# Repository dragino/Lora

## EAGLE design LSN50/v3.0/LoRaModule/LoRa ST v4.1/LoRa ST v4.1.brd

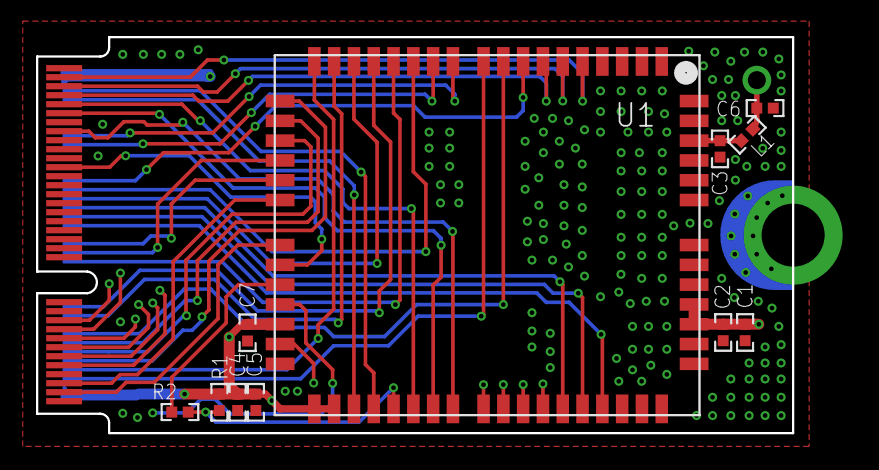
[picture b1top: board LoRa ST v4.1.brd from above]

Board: 4 copper layers, 42.0 x 22.0 mm, 13 parts (1 on the bottom side), 42 nets.

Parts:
C1, C4: 2.2uF; C0402
C2, C5, C7: 0.1uF; C0402
C3, C6: NC; C0402
L1: 9.1nH; L-0402
R1: 10K; R0402
R2: 2K; R0402
U1: LA66_APPLICATION_FRAME
U3: NGFF_M2_KEY_E_CORE; LORA_ST_PCB
U$2: LOGO-SILK-NEW

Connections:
GND: C1.1, C2.2, C3.1, C4.2, C5.1, C6.1, C7.1, U1.3, U1.31, U1.47, U1.48, U1.50, U1.54, U1.55, U1.58, U1.59, U1.61, U1.62, U3.1, U3.18, U3.57, U3.63, U3.75, U3.76
unnamed: C3.2, L1.1, U1.60
unnamed: C6.2, L1.2
PA0: U1.6, U3.71
PA1: U1.5, U3.73
PA2: U1.8, U3.50
PA3: U1.7, U3.69
PA4: U1.39, U3.61
PA5: U1.38, U3.65
PA6: U1.9, U3.16
PA7: U1.10, U3.6
PA8: U1.37, U3.67
PA9: U1.30, U3.17
PA11: R1.2, R2.1, U1.36
PA12: R2.2, U1.27
PA13: U1.28, U3.19
PA14: U1.11, U3.60
PA15: U1.12, U3.58
PB0: U1.34, U3.68
PB1: U1.35, U3.70
PB7: U1.13, U3.48
PB8: U1.15, U3.22
PB9: U1.14, U3.32
PB10: U1.17, U3.20
PB11: U1.16, U3.46
PB12: U1.19, U3.10
PB13: U1.18, U3.8
PB14: U1.20, U3.14
PB15: U1.21, U3.12
PC0: U1.44, U3.44
PC1: U1.43, U3.9
PC3: U1.46, U3.40
PC4: U1.45, U3.42
PC5: U1.42, U3.11
PC8: U1.41, U3.13
PC9: U1.40, U3.15
PC12: U1.22, U3.34
PC13: U1.23, U3.36
PD10: U1.25, U3.3
PD14: U1.24, U3.5
RSTN_PIN: U1.26, U3.53
VDD: C1.2, C2.1, C4.1, C5.2, C7.2, R1.1, U1.29, U1.32, U1.33, U1.52, U1.53, U3.2, U3.4, U3.72, U3.74

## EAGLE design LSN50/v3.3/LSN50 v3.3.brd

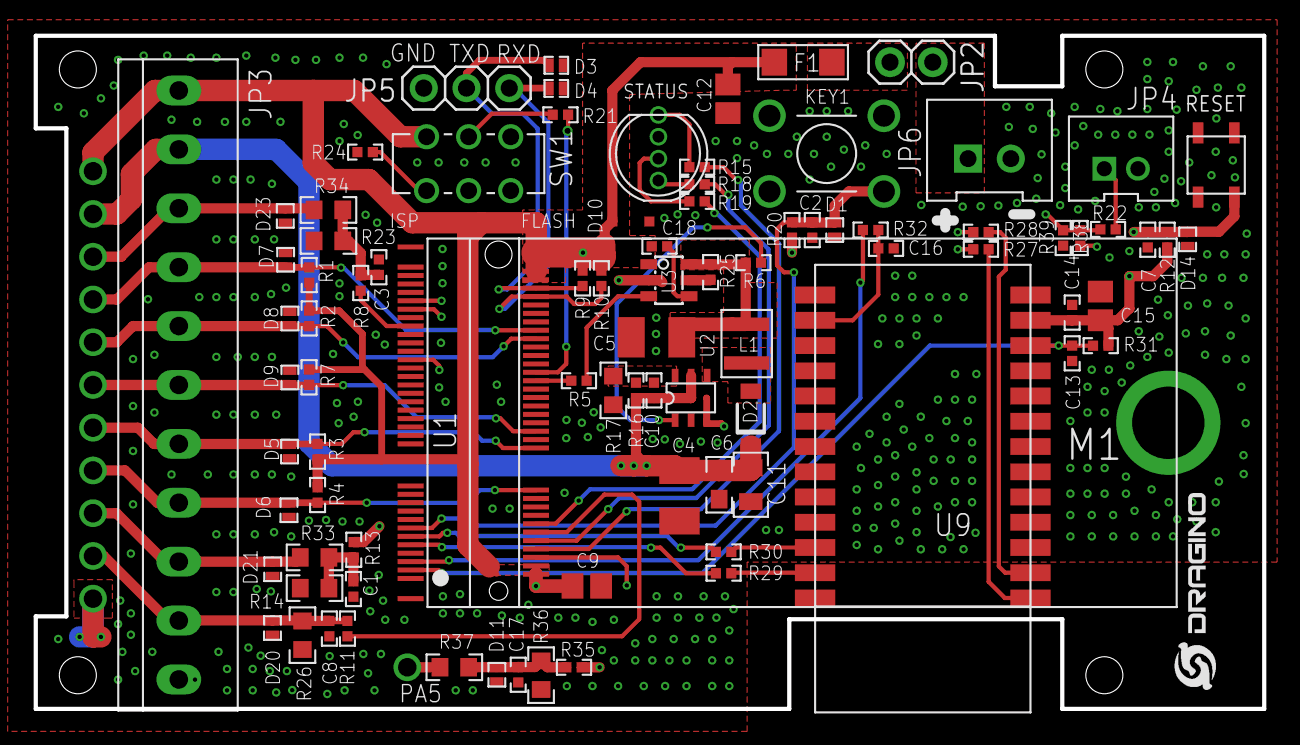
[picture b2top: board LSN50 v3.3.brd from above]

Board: 4 copper layers, 73.0 x 40.0 mm, 88 parts (0 on the bottom side), 52 nets.

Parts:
C1, C3, C8, C17: 3.3nF; C0402
C2, C13, C14, C16: 0.1uF; C0402
C4, C5: 100uF,10V; SMC_B
C6: 1uF 16V; C0603
C7: 330pF; C0402
C9, C12, C15: 10uF; C0805
C10, C18: 1nF; C0402
C11: 10uF，10V; C0805
D1, D3, D4, D5, D6, D7, D8, D9, D11, D14, D20, D21, D23: ESD; DFN1006
D2: 1N5819; SOD123FL
D10: PESD5V0S1BA; DIODE_SOD323-R
F1: MF-NSMF200-2; R1206
JP2: 1X02
JP3: KF350-11P
JP4: PH2.0-2P
JP5: 1X03
JP6: XH2.54-2P
KEY1: SWITCHDIL4; SWITCH_6X6X19_DIL4
L1: 4.7uH /SWPA3015S4R7MT; SWPA3010S
R1, R2, R6, R9, R10, R21, R24: 10K; R0402
R3, R4, R7, R12: 4.7K; R0402
R5, R8, R11, R13, R35: 1K; R0402
R14, R17, R23, R26, R36: 1M; R0603
R15, R18, R19, R25, R27, R28, R29, R30, R32: 2K; R0402
R16: 3M; R0402
R20, R22, R31: 100K; R0402
R33, R34, R37: 0R; R0603
R38, R39: 20K; R0402
RESET: 轻触开关3*3*1.5四脚贴片开关; SW4-SMD-3.35X3.35X1.5MM
STATUS: RGB-5M; RGB
SW1: MSS22D-18G2-2P2T-H2MM; MSS22D-18G2-2P2T-H2MM-DIL
U1: NGFF_M2_KEY_E_SHIELD_LA66; NGFF_M2_KEY_E_SHIELD
U2: RT9266; 6/SOT-23
U3: TPS22917; SOT23-6L
U9: BT24; BT24-SMD26
U$2: LOGO-NEW; LOGO-SILK-NEW

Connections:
+5V: C4.+, C6.2, C10.2, C11.2, D2.C, JP3.2, R16.1, U2.5
BATTERY: JP2.1, JP6.1
BOOT0: R21.1, U1.50
GND: C1.1, C2.1, C3.1, C4.-, C5.-, C6.1, C7.1, C8.1, C9.1, C11.1, C12.1, C13.2, C14.2, C15.1, C16.2, C17.1, D1.1, D3.1, D4.1, D5.1, D6.1, D7.1, D8.1, D9.1, D10.A, D11.1, D14.1, D20.1, D21.1, D23.1, JP3.11, JP4.2, JP5.3, JP6.2, KEY1.2, R14.2, R17.2, R23.2, R24.1, R26.2, R36.2, R39.2, RESET.B1, STATUS.2, SW1.1, U1.1, U1.18, U1.57, U1.63, U1.75, U1.76, U2.3, U3.2, U9.13, U9.14
unnamed: R15.1, STATUS.1
unnamed: R24.2, SW1.4
unnamed: R5.1, U3.3
unnamed: C10.1, R16.2, R17.1, U2.6
unnamed: D2.A, L1.P$2, U2.4
unnamed: R18.1, STATUS.4
unnamed: R6.2, U2.1
unnamed: R25.1, U3.5
unnamed: R19.1, STATUS.3
unnamed: C1.2, R13.1, R14.1, R33.2
unnamed: C5.+, L1.P$1, R6.1, R25.2, U3.6
unnamed: R27.1, U9.1
unnamed: R28.1, U9.2
unnamed: C16.1, R32.2, U9.15
unnamed: C3.2, R8.1, R23.1, R34.2
unnamed: R29.2, U9.25
unnamed: R30.2, U9.24
unnamed: C17.2, D11.2, R35.1, R36.1, R37.2
unnamed: R21.2, SW1.2
unnamed: C18.1, U3.4
unnamed: JP4.1, R22.1
NRST: C7.2, D14.2, R12.1, RESET.A1, U1.53
PA4: R8.2, U1.61
PA4_INPUT: D23.2, JP3.3, R34.1
PA5: R22.2, R35.2, R38.1, R39.1, U1.65
PA7: R38.2, U1.6
PA8: R13.2, U1.67
PA8_INPUT: D21.2, JP3.9, R33.1
PA14: D7.2, JP3.4, R1.1, U1.60
PA15: D8.2, JP3.5, R2.1, U1.58
PB7: R5.2, U1.48
PB8: D6.2, JP3.8, R4.1, U1.22
PB9: D5.2, JP3.7, R3.1, U1.32
PB12: R18.2, U1.10
PB13: R15.2, U1.8
PB14: R19.2, U1.14
PB15: R11.1, U1.12
PB15_INPUT: C8.2, D20.2, JP3.10, R11.2, R26.1
PC1: R29.1, U1.9
PC5: R30.1, U1.11
PC8: C2.2, D1.2, KEY1.1, R20.2, U1.13
PC13: D9.2, JP3.6, R7.1, U1.36
PD10: C13.1, R31.1, U1.3, U9.11
PD14: R32.1, U1.5
RXD: D4.2, JP5.1, R10.1, R27.2, U1.68
TXD: D3.2, JP5.2, R9.1, R28.2, U1.70
VBAT: F1.2, JP2.2
VDD: C9.2, C12.2, C14.1, C15.2, C18.2, D10.C, F1.1, JP3.1, R1.2, R2.2, R3.2, R4.2, R7.2, R9.2, R10.2, R12.2, R20.1, R31.2, SW1.3, U1.2, U1.4, U1.72, U1.74, U3.1, U9.12

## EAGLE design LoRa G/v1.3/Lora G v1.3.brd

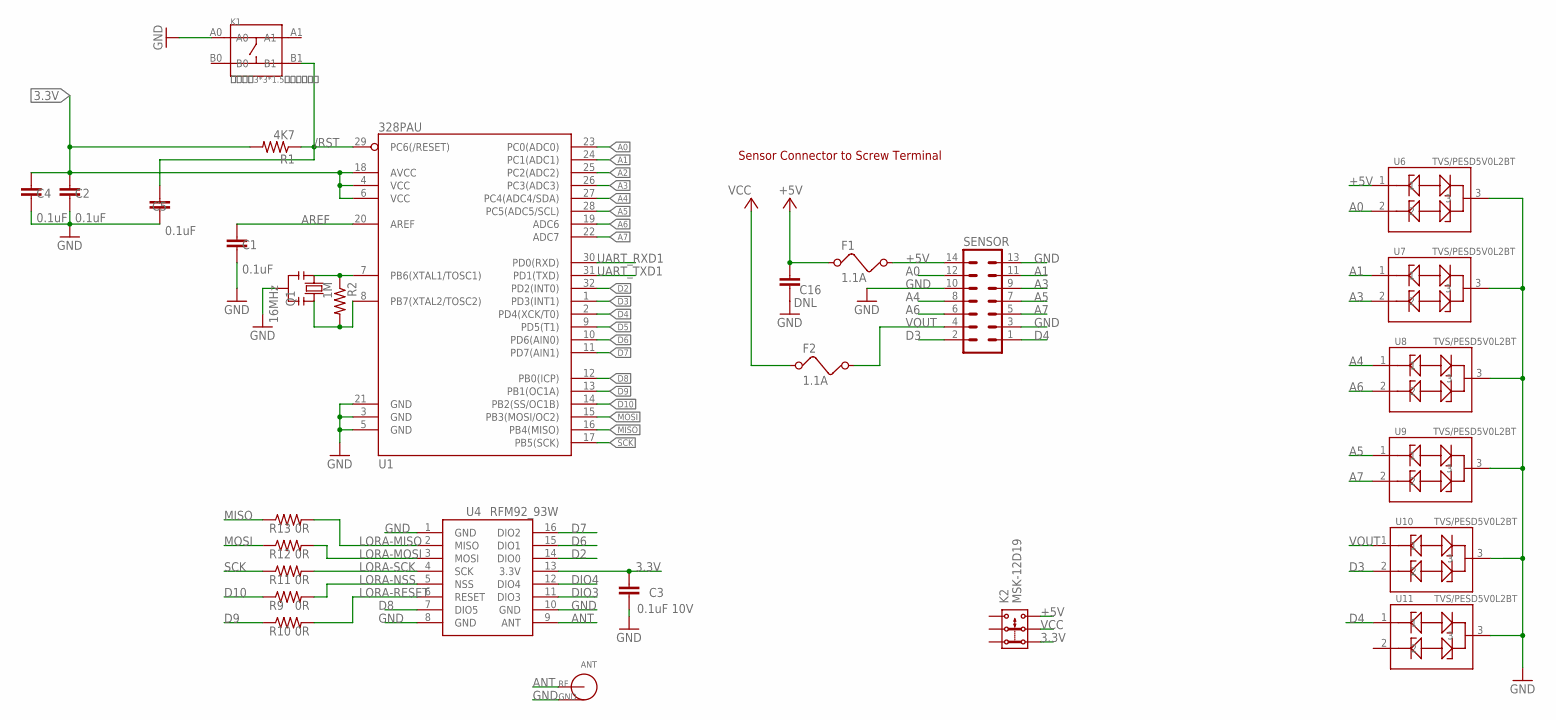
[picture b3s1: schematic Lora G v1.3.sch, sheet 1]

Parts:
ANT: I-PEX
C1, C2, C4, C5: 0.1uF; C0402
C3: 0.1uF 10V; C0402
C16: DNL; C0402
F1, F2: 1.1A; L1812
K1: 轻触开关3*3*1.5四脚贴片开关; SW4-SMD-3.35X3.35X1.5MM
K2: MSK-12D19
Q1: 16MHz; RESONATOR
R1: 4K7; R0402
R2: 1M; R0402
R9, R10, R11, R12, R13: 0R; R0402
SENSOR: MA07-2
U1: 328PAU
U4: RFM92_93W
U6, U7, U8, U9, U10, U11: TVS/PESD5V0L2BT; SOT23

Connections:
3.3V: C2.2, C3.2, C4.2, K2.1.2, R1.2, U1.4 (VCC), U1.6 (VCC), U1.18 (AVCC), U4.13 (3.3V); also elsewhere on the board
+5V: C16.1, F1.1, K2.3.2, U6.1; also elsewhere on the board
/RST: C5.2, K1.B1, R1.1, U1.29 (PC6(/RESET)); also elsewhere on the board
A0: SENSOR.12, U1.23 (PC0(ADC0)), U6.2
A1: SENSOR.11, U1.24 (PC1(ADC1)), U7.1
A2: U1.25 (PC2(ADC2)); also elsewhere on the board
A3: SENSOR.9, U1.26 (PC3(ADC3)), U7.2
A4: SENSOR.8, U1.27 (PC4(ADC4/SDA)), U8.1
A5: SENSOR.7, U1.28 (PC5(ADC5/SCL)), U9.1
A6: SENSOR.6, U1.19 (ADC6), U8.2
A7: SENSOR.5, U1.22 (ADC7), U9.2
ANT: ANT.SIG, U4.9 (ANT)
AREF: C1.2, U1.20 (AREF)
D2: U1.32 (PD2(INT0)), U4.14 (DIO0)
D3: SENSOR.2, U1.1 (PD3(INT1)), U10.2
D4: SENSOR.1, U1.2 (PD4(XCK/T0)), U11.1
D5: U1.9 (PD5(T1)); also elsewhere on the board
D6: U1.10 (PD6(AIN0)), U4.15 (DIO1)
D7: U1.11 (PD7(AIN1)), U4.16 (DIO2)
D8: U1.12 (PB0(ICP)), U4.7 (DIO5)
D9: R10.1, U1.13 (PB1(OC1A))
D10: R9.1, U1.14 (PB2(SS/OC1B)); also elsewhere on the board
DIO3: U4.11 (DIO3)
DIO4: U4.12 (DIO4)
GND: ANT.GND, ANT.GND1 (GND), C1.1, C2.1, C3.1, C4.1, C5.1, C16.2, K1.A0, Q1.2, SENSOR.3, SENSOR.10, SENSOR.13, U1.3 (GND), U1.5 (GND), U1.21 (GND), U4.1 (GND), U4.8 (GND), U4.10 (GND), U6.3, U7.3, U8.3, U9.3, U10.3, U11.3; also elsewhere on the board
LORA-MISO: R13.2, U4.2 (MISO)
LORA-MOSI: R12.2, U4.3 (MOSI)
LORA-NSS: R9.2, U4.5 (NSS)
LORA-RESET: R10.2, U4.6 (RESET)
LORA-SCK: R11.2, U4.4 (SCK)
MISO: R13.1, U1.16 (PB4(MISO)); also elsewhere on the board
MOSI: R12.1, U1.15 (PB3(MOSI/OC2)); also elsewhere on the board
unnamed: Q1.3, R2.2, U1.8 (PB7(XTAL2/TOSC2))
unnamed: Q1.1, R2.1, U1.7 (PB6(XTAL1/TOSC1))
unnamed: F1.2, SENSOR.14
SCK: R11.1, U1.17 (PB5(SCK)); also elsewhere on the board
UART_RXD1: U1.30 (PD0(RXD)); also elsewhere on the board
UART_TXD1: U1.31 (PD1(TXD)); also elsewhere on the board
VCC: F2.1, K2.2.2
VOUT: F2.2, SENSOR.4, U10.1

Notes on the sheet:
Sensor Connector to Screw Terminal

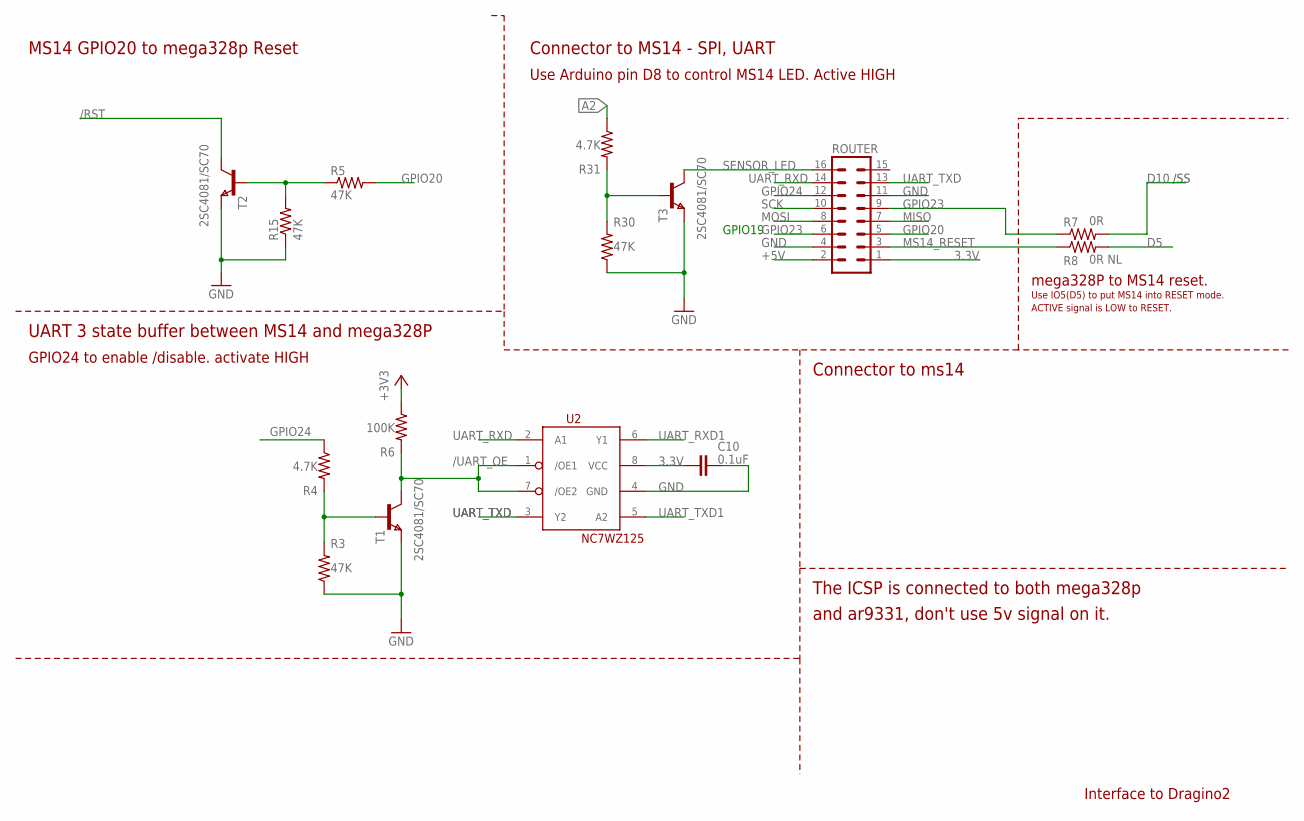
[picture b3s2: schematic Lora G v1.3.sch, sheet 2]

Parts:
C10: 0.1uF; C0402
R3, R5, R15, R30: 47K; R0402
R4, R31: 4.7K; R0402
R6: 100K; R0402
R7: 0R; R0402
R8: 0R NL; R0805
ROUTER: MA08-2
T1, T3: 2SC4081/SC70; SOT323
T2: 2SC4081/SC70; SOT323; MPN DSS4160U-7
U2: NC7WZ125; US8

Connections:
3.3V: C10.2, R6.1, ROUTER.1, U2.8 (VCC); also elsewhere on the board
+5V: ROUTER.2; also elsewhere on the board
/RST: T2.1 (C); also elsewhere on the board
/UART_OE: R6.2, T1.1 (C), U2.1 (/OE1), U2.7 (/OE2)
A2: R31.1; also elsewhere on the board
D5: R8.2; also elsewhere on the board
D10: R7.2; also elsewhere on the board
GND: C10.1, R3.1, R15.1, R30.1, ROUTER.4, ROUTER.11, T1.3 (E), T2.3 (E), T3.3 (E), U2.4 (GND); also elsewhere on the board
GPIO20: R5.2, ROUTER.5
GPIO23: R7.1, ROUTER.6, ROUTER.9
GPIO24: R4.1, ROUTER.12
MISO: ROUTER.7; also elsewhere on the board
MOSI: ROUTER.8; also elsewhere on the board
MS14_RESET: R8.1, ROUTER.3
unnamed: R3.2, R4.2, T1.2 (B)
unnamed: R5.1, R15.2, T2.2 (B)
unnamed: R30.2, R31.2, T3.2 (B)
SCK: ROUTER.10; also elsewhere on the board
SENSOR_LED: ROUTER.16, T3.1 (C)
UART_RXD: ROUTER.14, U2.2 (A1)
UART_RXD1: U2.6 (Y1); also elsewhere on the board
UART_TXD: ROUTER.13, U2.3 (Y2)
UART_TXD1: U2.5 (A2); also elsewhere on the board

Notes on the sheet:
UART 3 state buffer between MS14 and mega328P
Interface to Dragino2
The ICSP is connected to both mega328p
and ar9331, don't use 5v signal on it.
Connector to ms14
Connector to MS14 - SPI, UART
MS14 GPIO20 to mega328p Reset
GPIO24 to enable /disable. activate HIGH
mega328P to MS14 reset.
Use IO5(D5) to put MS14 into RESET mode.
ACTIVE signal is LOW to RESET.
Use Arduino pin D8 to control MS14 LED. Active HIGH
/SS
GPIO19

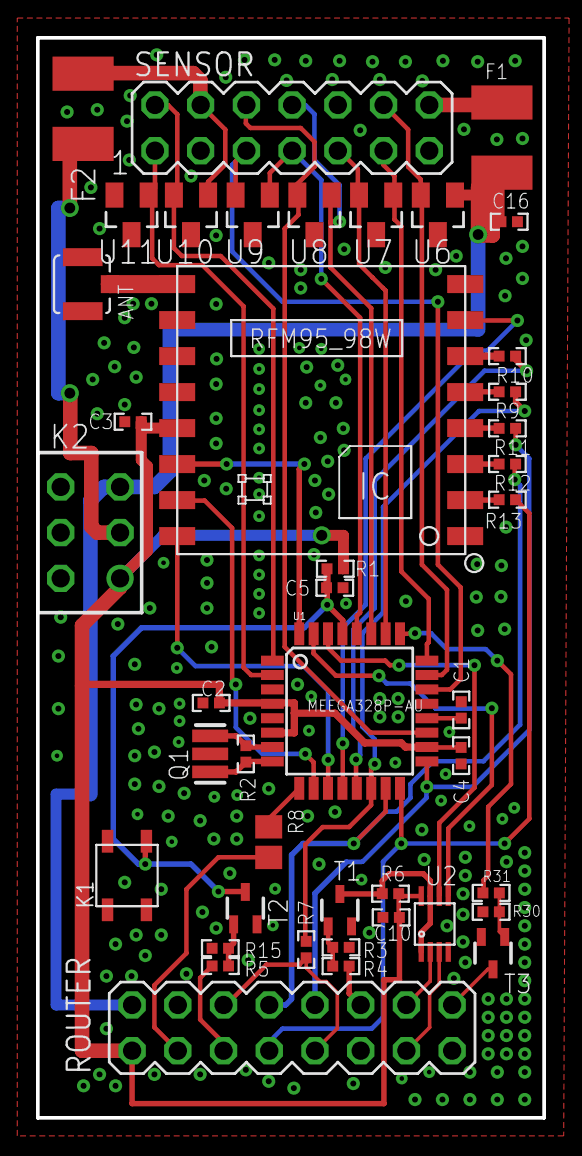
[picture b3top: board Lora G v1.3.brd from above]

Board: 2 copper layers, 28.1 x 60.0 mm, 44 parts (1 on the bottom side), 49 nets.

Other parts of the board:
U$1: LOGO-SILK-NEW

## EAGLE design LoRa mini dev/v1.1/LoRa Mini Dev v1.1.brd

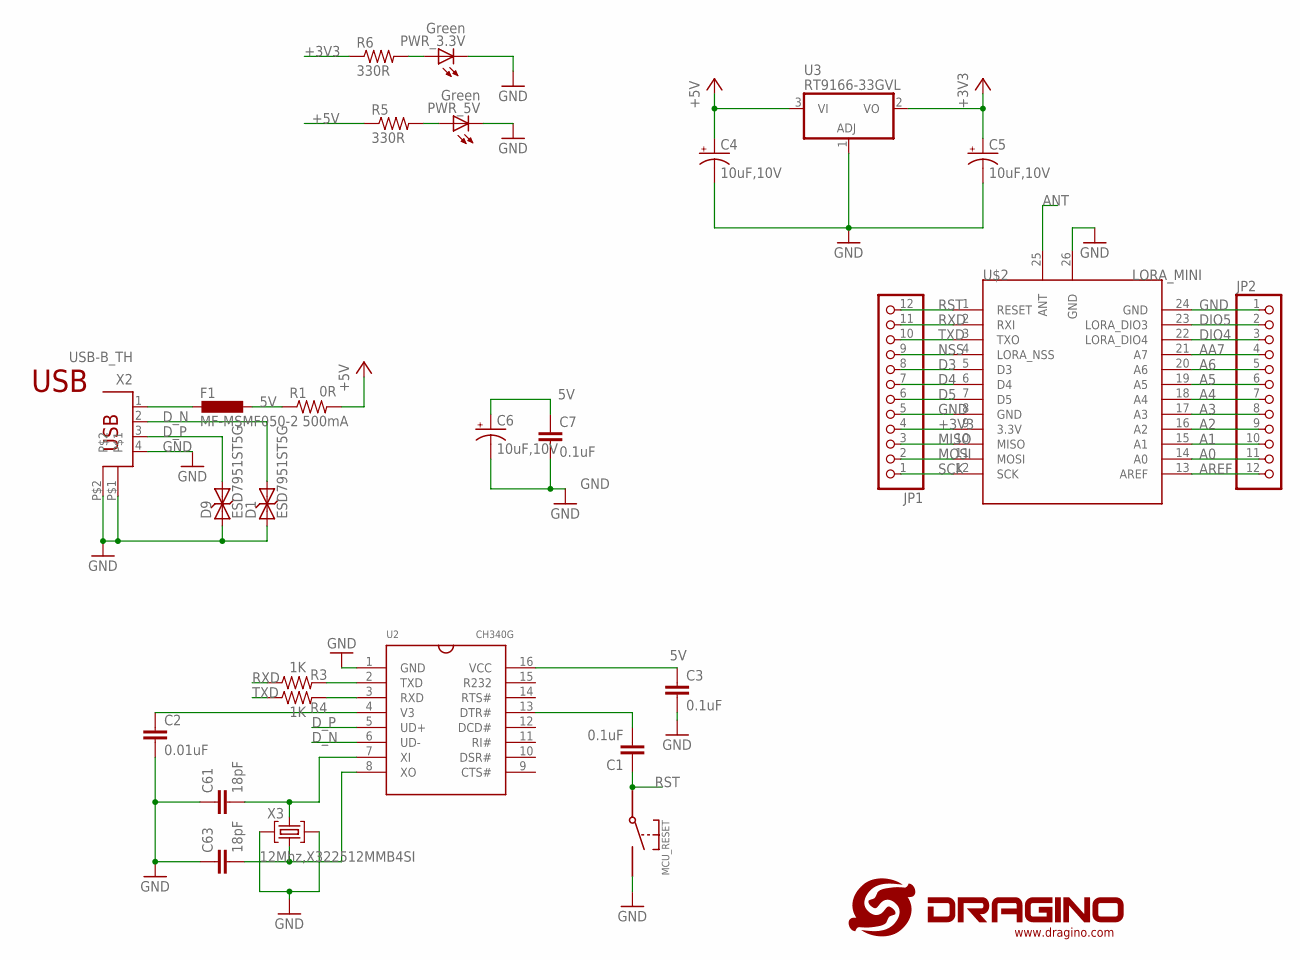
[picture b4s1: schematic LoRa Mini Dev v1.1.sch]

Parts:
C1, C3, C7: 0.1uF; C0402
C2: 0.01uF; C0402
C4, C5, C6: 10uF,10V; SMC_A
C61, C63: 18pF; C0402
D1, D9: ESD7951ST5G; SOD−923
F1: MF-MSMF050-2 500mA; L1812
JP1, JP2: PINHD-1X12; 1X12
MCU_RESET: SWITCH; SWITCH_3X6X5MM
PWR_3.3V, PWR_5V: Green; DRAGINO_CHIPLED_0603
R1: 0R; M0805
R3, R4: 1K; R0402
R5, R6: 330R; R0402
U2: CH340G
U3: RT9166-33GVL; SOT23
U$1: LOGO-NEW; LOGO-SILK-NEW
U$2: LORA_MINI; LORA_MINI_PCB
X2: USB-B_TH; PN61729
X3: 12Mhz,X322512MMB4SI; SMARTPRJ_CRYSTAL-3.2-2.5

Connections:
5V: C3.1, C6.+, C7.1, F1.1, R1.1, U2.16 (VCC)
+3V3: C5.+, JP1.4, R6.1, U3.2 (VO), U$2.9 (3.3V)
+5V: C4.+, R1.2, R5.1, U3.3 (VI)
A0: JP2.11, U$2.14 (A0)
A1: JP2.10, U$2.15 (A1)
A2: JP2.9, U$2.16 (A2)
A3: JP2.8, U$2.17 (A3)
A4: JP2.7, U$2.18 (A4)
A5: JP2.6, U$2.19 (A5)
A6: JP2.5, U$2.20 (A6)
AA7: JP2.4, U$2.21 (A7)
ANT: U$2.25 (ANT)
AREF: JP2.12, U$2.13 (AREF)
CLK_N: C63.2, U2.8 (XO), X3.1 (C1)
CLK_P: C61.2, U2.7 (XI), X3.3 (C2)
D3: JP1.8, U$2.5 (D3)
D4: JP1.7, U$2.6 (D4)
D5: JP1.6, U$2.7 (D5)
DIO4: JP2.3, U$2.22 (LORA_DIO4)
DIO5: JP2.2, U$2.23 (LORA_DIO3)
DTR: C1.2, U2.13 (DTR#)
D_N: D1.P$2 (2), U2.6 (UD-), X2.2
D_P: D9.P$2 (2), U2.5 (UD+), X2.3
GND: C2.2, C3.2, C4.-, C5.-, C6.-, C7.2, C61.1, C63.1, D1.P$1 (1), D9.P$1 (1), JP1.5, JP2.1, MCU_RESET.P$2, PWR_3.3V.C, PWR_5V.C, U2.1 (GND), U3.1 (ADJ), U$2.8 (GND), U$2.24 (GND), U$2.26 (GND), X2.4, X2.P$1, X2.P$2, X3.2 (GND), X3.4 (GND)
MISO: JP1.3, U$2.10 (MISO)
MOSI: JP1.2, U$2.11 (MOSI)
unnamed: PWR_3.3V.A, R6.2
unnamed: F1.2, X2.1
unnamed: R3.2, U2.2 (TXD)
unnamed: R4.2, U2.3 (RXD)
unnamed: PWR_5V.A, R5.2
unnamed: C2.1, U2.4 (V3)
NSS: JP1.9, U$2.4 (LORA_NSS)
RST: C1.1, JP1.12, MCU_RESET.P$1, U$2.1 (RESET)
RXD: JP1.11, R3.1, U$2.2 (RXI)
SCK: JP1.1, U$2.12 (SCK)
TXD: JP1.10, R4.1, U$2.3 (TXO)

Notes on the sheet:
USB

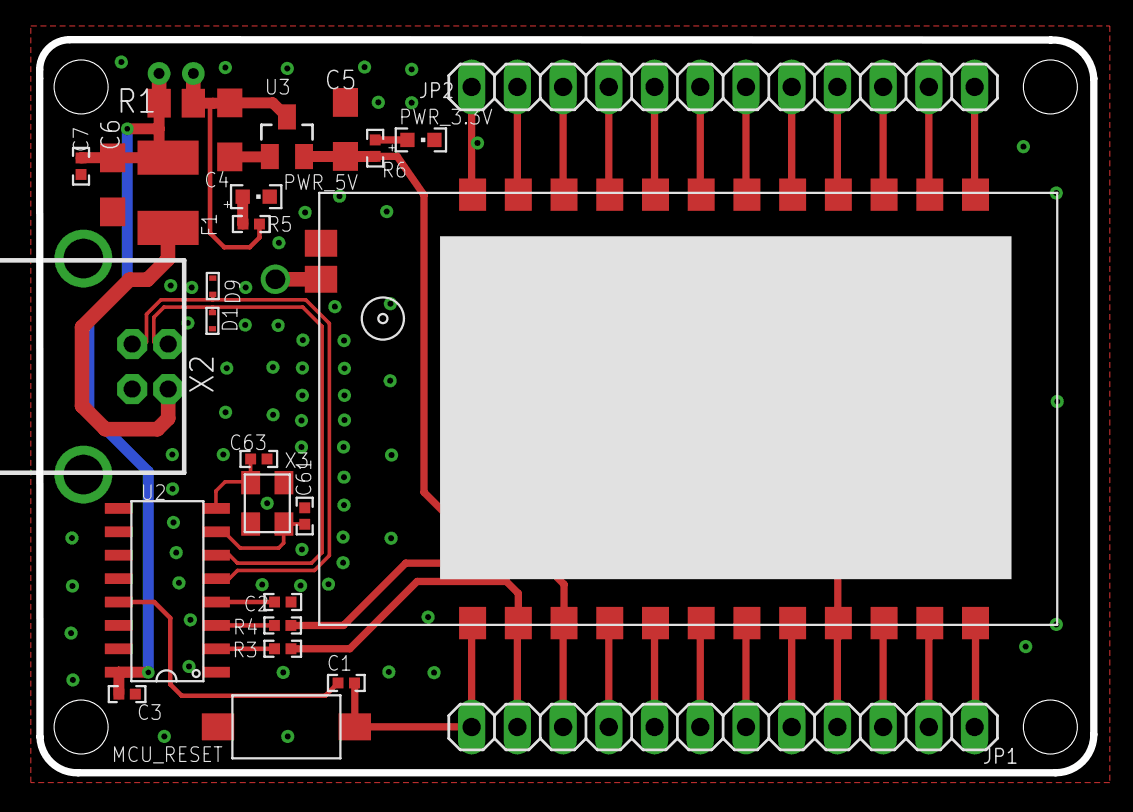
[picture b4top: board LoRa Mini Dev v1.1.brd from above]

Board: 2 copper layers, 58.6 x 40.7 mm, 28 parts (1 on the bottom side), 36 nets.

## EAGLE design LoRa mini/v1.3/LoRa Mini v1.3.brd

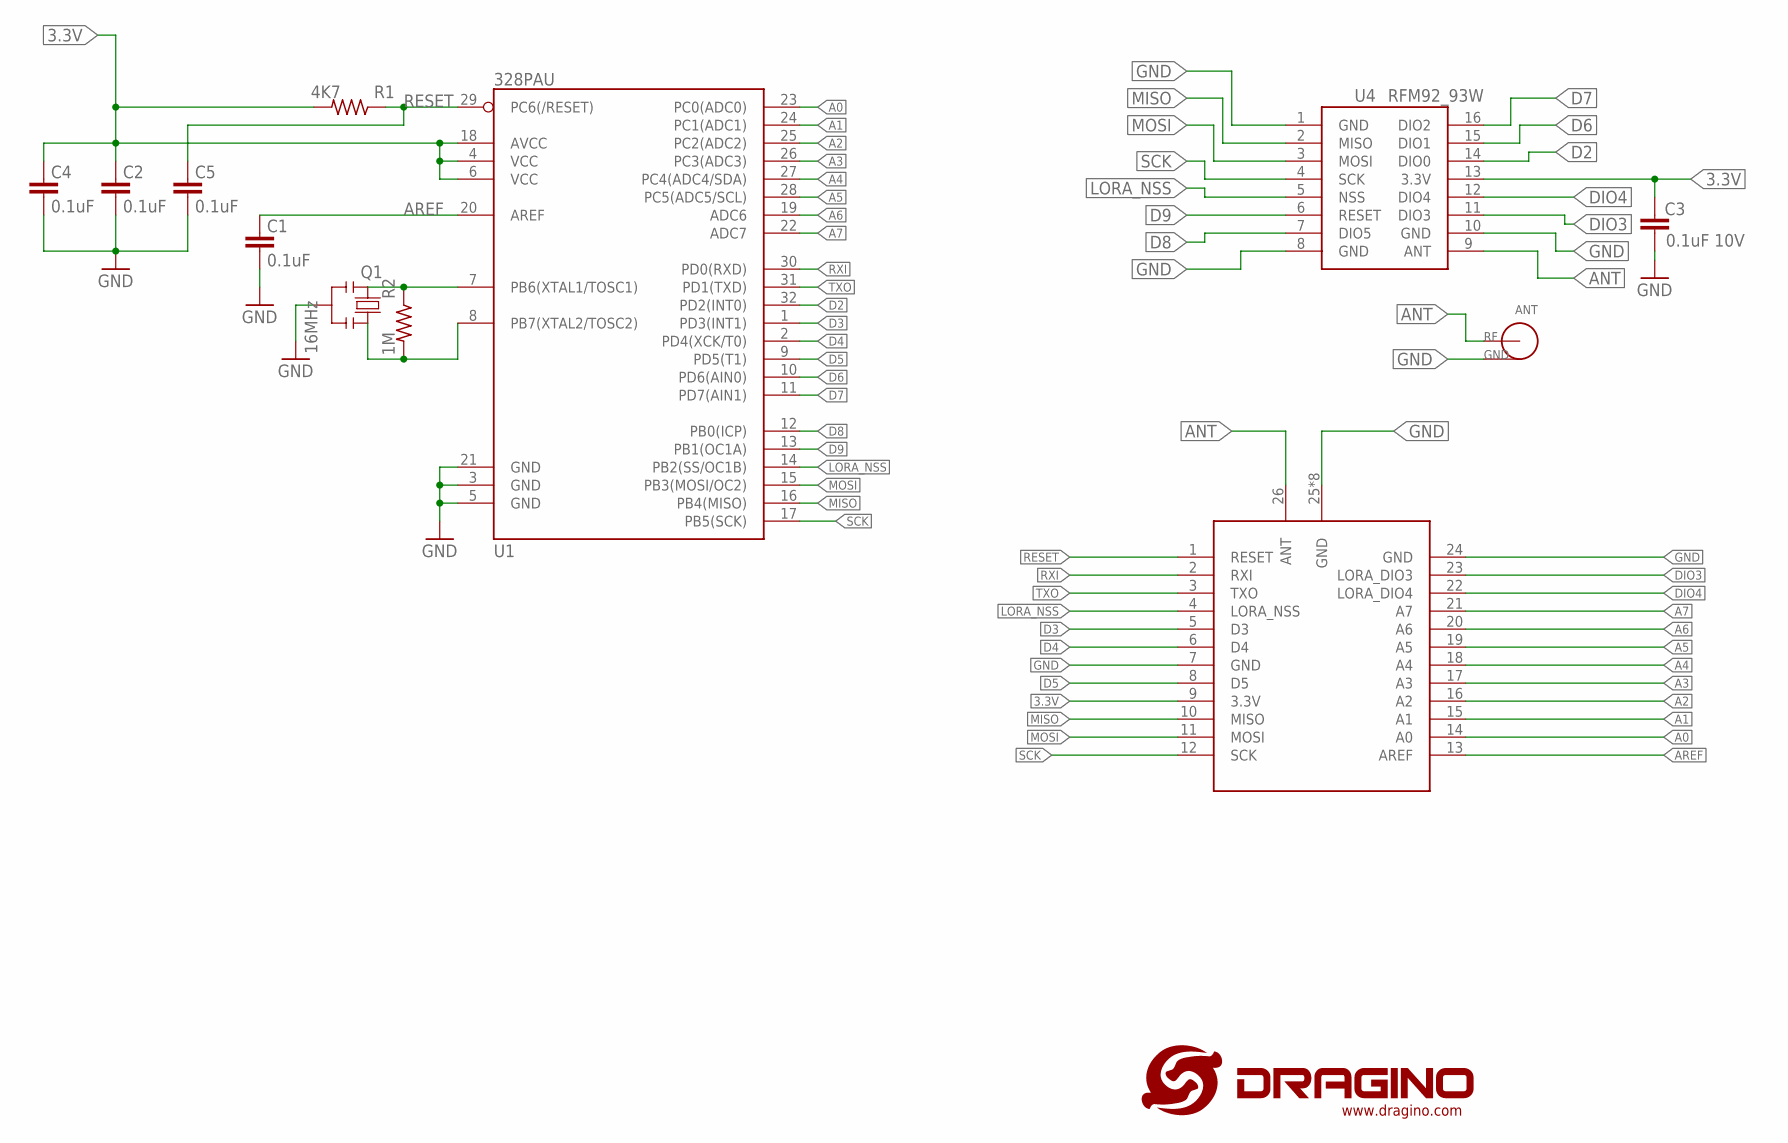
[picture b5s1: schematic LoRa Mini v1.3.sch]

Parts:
ANT: I-PEX
C1, C2, C4, C5: 0.1uF; C0402
C3: 0.1uF 10V; C0402
Q1: 16MHz; RESONATOR
R1: 4K7; R0402
R2: 1M; R0402
U1: 328PAU
U4: RFM92_93W
U$1: LORA328P_PCB

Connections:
3.3V: C2.2, C3.2, C4.2, R1.2, U1.4 (VCC), U1.6 (VCC), U1.18 (AVCC), U4.13 (3.3V), U$1.9 (3.3V)
A0: U1.23 (PC0(ADC0)), U$1.14 (A0)
A1: U1.24 (PC1(ADC1)), U$1.15 (A1)
A2: U1.25 (PC2(ADC2)), U$1.16 (A2)
A3: U1.26 (PC3(ADC3)), U$1.17 (A3)
A4: U1.27 (PC4(ADC4/SDA)), U$1.18 (A4)
A5: U1.28 (PC5(ADC5/SCL)), U$1.19 (A5)
A6: U1.19 (ADC6), U$1.20 (A6)
A7: U1.22 (ADC7), U$1.21 (A7)
ANT: ANT.SIG, U4.9 (ANT), U$1.26 (ANT)
AREF: C1.2, U1.20 (AREF), U$1.13 (AREF)
D2: U1.32 (PD2(INT0)), U4.14 (DIO0)
D3: U1.1 (PD3(INT1)), U$1.5 (D3)
D4: U1.2 (PD4(XCK/T0)), U$1.6 (D4)
D5: U1.9 (PD5(T1)), U$1.8 (D5)
D6: U1.10 (PD6(AIN0)), U4.15 (DIO1)
D7: U1.11 (PD7(AIN1)), U4.16 (DIO2)
D8: U1.12 (PB0(ICP)), U4.7 (DIO5)
D9: U1.13 (PB1(OC1A)), U4.6 (RESET)
DIO3: U4.11 (DIO3), U$1.23 (LORA_DIO3)
DIO4: U4.12 (DIO4), U$1.22 (LORA_DIO4)
GND: ANT.GND, ANT.GND1 (GND), C1.1, C2.1, C3.1, C4.1, C5.1, Q1.2, U1.3 (GND), U1.5 (GND), U1.21 (GND), U4.1 (GND), U4.8 (GND), U4.10 (GND), U$1.7 (GND), U$1.24 (GND), U$1.25 (GND), U$1.P$1 (GND), U$1.P$2 (GND), U$1.P$3 (GND), U$1.P$4 (GND), U$1.P$5 (GND), U$1.P$6 (GND), U$1.P$7 (GND)
LORA_NSS: U1.14 (PB2(SS/OC1B)), U4.5 (NSS), U$1.4 (LORA_NSS)
MISO: U1.16 (PB4(MISO)), U4.2 (MISO), U$1.10 (MISO)
MOSI: U1.15 (PB3(MOSI/OC2)), U4.3 (MOSI), U$1.11 (MOSI)
unnamed: Q1.3, R2.2, U1.8 (PB7(XTAL2/TOSC2))
unnamed: Q1.1, R2.1, U1.7 (PB6(XTAL1/TOSC1))
RESET: C5.2, R1.1, U1.29 (PC6(/RESET)), U$1.1 (RESET)
RXI: U1.30 (PD0(RXD)), U$1.2 (RXI)
SCK: U1.17 (PB5(SCK)), U4.4 (SCK), U$1.12 (SCK)
TXO: U1.31 (PD1(TXD)), U$1.3 (TXO)

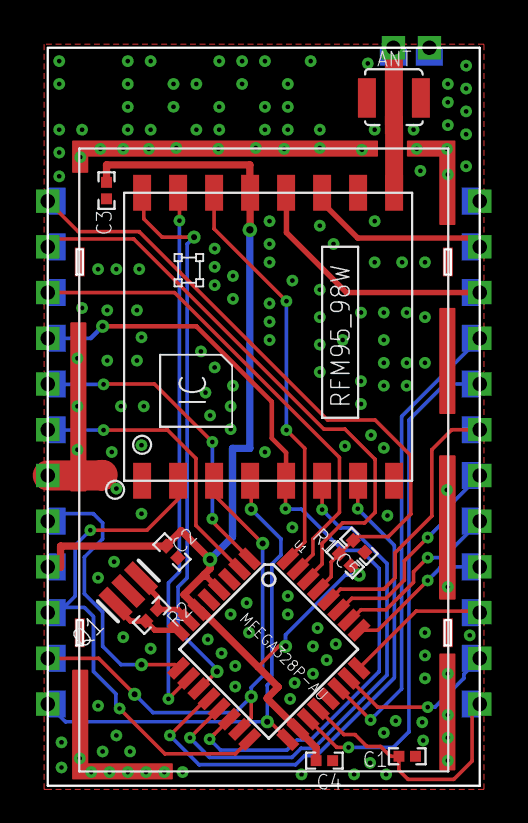
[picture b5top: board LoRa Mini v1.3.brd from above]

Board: 2 copper layers, 24.0 x 41.0 mm, 13 parts (1 on the bottom side), 31 nets.

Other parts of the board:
U$3: LOGO-SILK-NEW

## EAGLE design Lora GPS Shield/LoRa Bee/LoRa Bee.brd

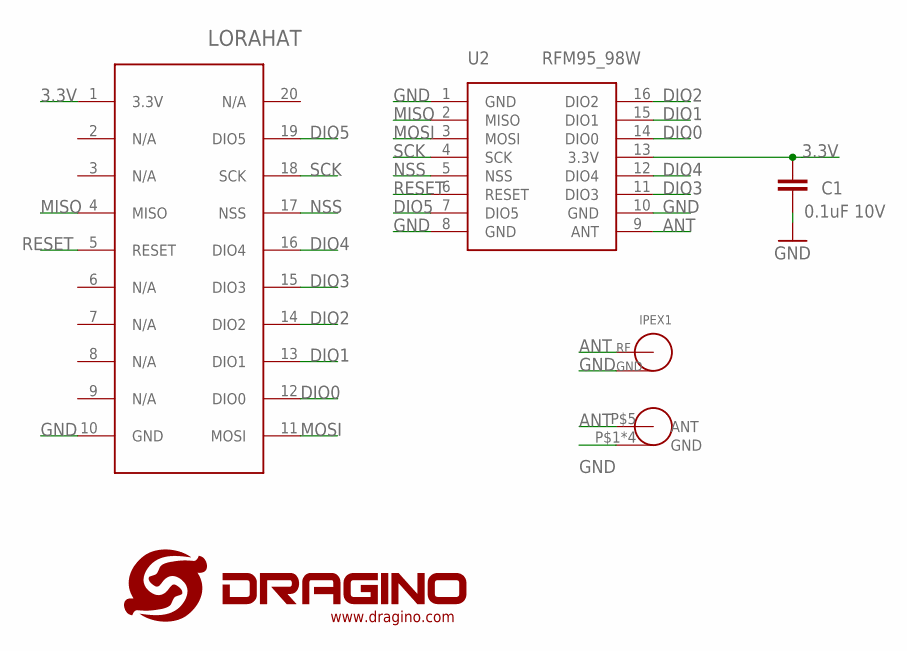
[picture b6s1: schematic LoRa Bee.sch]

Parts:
C1: 0.1uF 10V; C0402
IPEX1: I-PEX
U1: LORAHAT
U2: RFM95_98W
U$1: LOGO-NEW; LOGO-SILK-NEW
X4: SMA-KE

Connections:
3.3V: C1.2, U1.1 (3.3V), U2.13 (3.3V)
ANT: IPEX1.SIG, U2.9 (ANT), X4.P$5 (ANT)
DIO0: U1.12 (DIO0), U2.14 (DIO0)
DIO1: U1.13 (DIO1), U2.15 (DIO1)
DIO2: U1.14 (DIO2), U2.16 (DIO2)
DIO3: U1.15 (DIO3), U2.11 (DIO3)
DIO4: U1.16 (DIO4), U2.12 (DIO4)
DIO5: U1.19 (DIO5), U2.7 (DIO5)
GND: C1.1, IPEX1.GND, IPEX1.GND1 (GND), U1.10 (GND), U2.1 (GND), U2.8 (GND), U2.10 (GND), X4.P$1 (GND), X4.P$2 (GND), X4.P$3 (GND), X4.P$4 (GND)
MISO: U1.4 (MISO), U2.2 (MISO)
MOSI: U1.11 (MOSI), U2.3 (MOSI)
NSS: U1.17 (NSS), U2.5 (NSS)
RESET: U1.5 (RESET), U2.6 (RESET)
SCK: U1.18 (SCK), U2.4 (SCK)

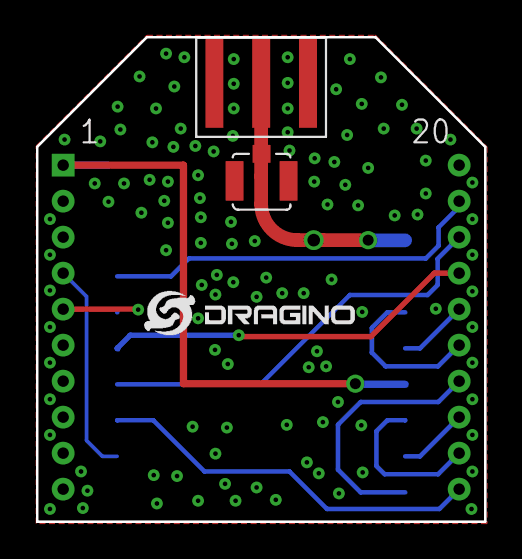
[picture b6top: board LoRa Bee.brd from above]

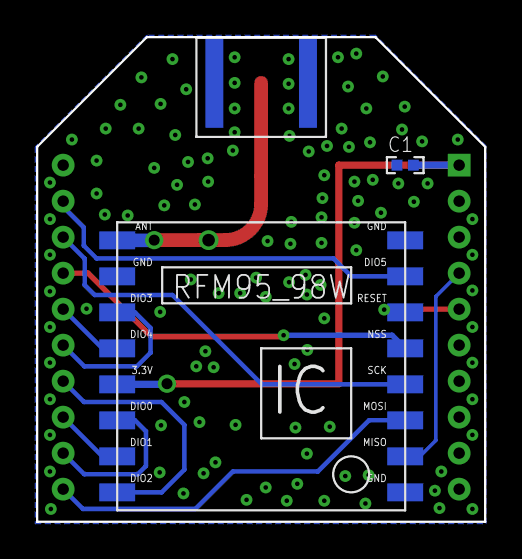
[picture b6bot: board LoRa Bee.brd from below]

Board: 2 copper layers, 24.9 x 26.9 mm, 6 parts (2 on the bottom side), 14 nets.

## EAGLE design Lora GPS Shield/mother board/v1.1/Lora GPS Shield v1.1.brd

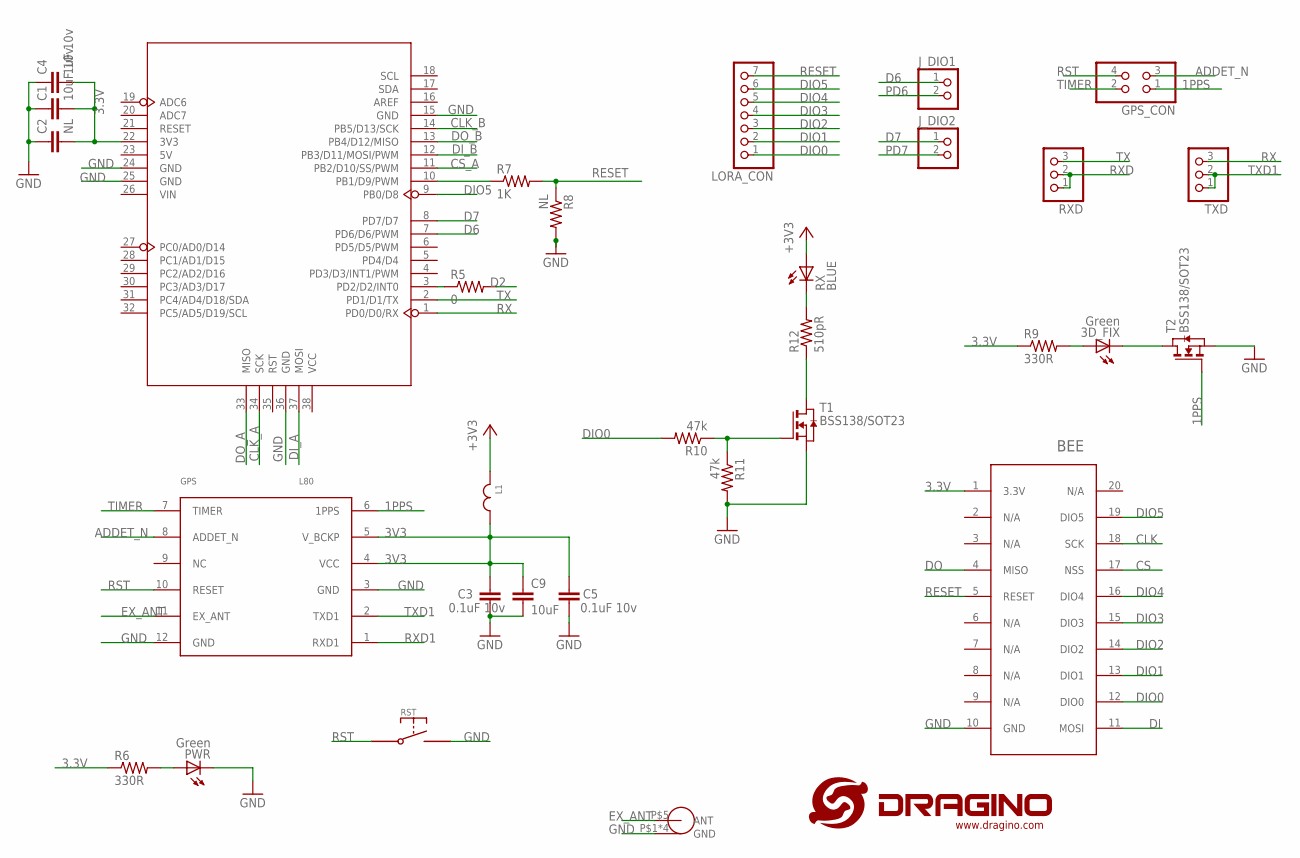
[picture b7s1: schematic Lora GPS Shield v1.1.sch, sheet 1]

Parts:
3D_FIX: Green; CHIPLED_0603
C1: 10uF 10v; C0805
C2: NL; C0402
C3, C5: 0.1uF 10v; C0402
C4: 1uF 10v; C0402
C9: 10uF; C0805
GPS: L80
GPS_ANT: NL; SMA-KE
GPS_CON: PINHD-2X2; 2X02
J_DIO1: PINHD-1X21X2_S; 1X02
J_DIO2: PINHD-1X2; 1X02
L1: JLC-PZ2012D800-3R0TF; C0805
LORA_CON: PINHD-1X71X7_S; 1X07
PWR: Green; DRAGINO_CHIPLED_0603
R5: 0; R0402
R6, R9: 330R; R0402
R7: 1K; R0402
R8: NL; R0402
R10, R11: 47k; R0402
R12: 510pR; R0402
RST: SWITCHTS-017; TS-017
RX: BLUE; CHIPLED_0603
RXD: PINHD-1X3; 1X03
T1, T2: BSS138/SOT23; SOT-23
TXD: PINHD-1X3; 1X03
U3: BEE; LORA
U5: MOUDLE_ARDUINO-38PMOUDLE_ARDUINO-38P_L; MOUDLE_ARDUINO-38P_L
U$1: LOGO-NEW; LOGO-SILK-NEW

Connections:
1PPS: GPS.6 (1PPS), GPS_CON.1, T2.3 (G)
3.3V: C1.2, C2.2, C4.2, L1.1, R6.1, R9.1, RX.A, U3.1 (3.3V), U5.22 (3V3); also elsewhere on the board
3V3: C3.2, C5.2, C9.1, GPS.4 (VCC), GPS.5 (V_BCKP), L1.2
/RESET: R12.1, T1.1 (D)
ADDET_N: GPS.8 (ADDET_N), GPS_CON.3
CLK: U3.18 (SCK); also elsewhere on the board
CLK_A: U5.34 (SCK); also elsewhere on the board
CLK_B: U5.14 (PB5/D13/SCK); also elsewhere on the board
CS: U3.17 (NSS); also elsewhere on the board
CS_A: U5.11 (PB2/D10/SS/PWM); also elsewhere on the board
D2: R5.2; also elsewhere on the board
D6: J_DIO1.1, U5.7 (PD6/D6/PWM)
D7: J_DIO2.1, U5.8 (PD7/D7)
DI: U3.11 (MOSI); also elsewhere on the board
DIO0: LORA_CON.1, R10.2, U3.12 (DIO0); also elsewhere on the board
DIO1: LORA_CON.2, U3.13 (DIO1); also elsewhere on the board
DIO2: LORA_CON.3, U3.14 (DIO2); also elsewhere on the board
DIO3: LORA_CON.4, U3.15 (DIO3)
DIO4: LORA_CON.5, U3.16 (DIO4)
DIO5: LORA_CON.6, U3.19 (DIO5), U5.9 (PB0/D8)
DI_A: U5.37 (MOSI); also elsewhere on the board
DI_B: U5.12 (PB3/D11/MOSI/PWM); also elsewhere on the board
DO: U3.4 (MISO); also elsewhere on the board
DO_A: U5.33 (MISO); also elsewhere on the board
DO_B: U5.13 (PB4/D12/MISO); also elsewhere on the board
EX_ANT: GPS.11 (EX_ANT), GPS_ANT.P$5 (ANT)
GND: C1.1, C2.1, C3.1, C4.1, C5.1, C9.2, GPS.3 (GND), GPS.12 (GND), GPS_ANT.P$1 (GND), GPS_ANT.P$2 (GND), GPS_ANT.P$3 (GND), GPS_ANT.P$4 (GND), PWR.C, R8.2, R11.2, RST.P$2, T1.2 (S), T2.2 (S), U3.10 (GND), U5.15 (GND), U5.24 (GND), U5.25 (GND), U5.36 (GND); also elsewhere on the board
unnamed: R5.1, U5.3 (PD2/D2/INT0)
unnamed: PWR.A, R6.2
unnamed: R7.1, U5.10 (PB1/D9/PWM)
unnamed: 3D_FIX.A, R9.2
unnamed: 3D_FIX.C, T2.1 (D)
unnamed: R10.1, R11.1, T1.3 (G)
unnamed: R12.2, RX.C
PD6: J_DIO1.2; also elsewhere on the board
PD7: J_DIO2.2; also elsewhere on the board
RESET: LORA_CON.7, R7.2, R8.1, U3.5 (RESET)
RST: GPS.10 (RESET), GPS_CON.4, RST.P$1
RX: TXD.3, U5.1 (PD0/D0/RX)
RXD: RXD.1, RXD.2; also elsewhere on the board
RXD1: GPS.1 (RXD1); also elsewhere on the board
TIMER: GPS.7 (TIMER), GPS_CON.2
TX: RXD.3, U5.2 (PD1/D1/TX)
TXD1: GPS.2 (TXD1), TXD.1, TXD.2

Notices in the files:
parts and their libraries:
dragino: http://creativecommons.org/licenses/by-sa/3.0
dragino: Released under the CC Attribution Share-Alike 3.0 License
